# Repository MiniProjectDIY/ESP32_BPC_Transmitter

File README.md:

# ESP32_BPC_Transmitter
Trasmit BPC time signal with ESP32 and a customized PCB

https://youtu.be/aWq-_jqWnzw

Hardware:Fine tune the LC parameter to 68.5Khz resonance frequency

Software:Modify the wifi ssid and wifi password,flash the micropython firmware and upload the python code

The transmission distance is approximately two meters, but it will vary depending on your inductor.

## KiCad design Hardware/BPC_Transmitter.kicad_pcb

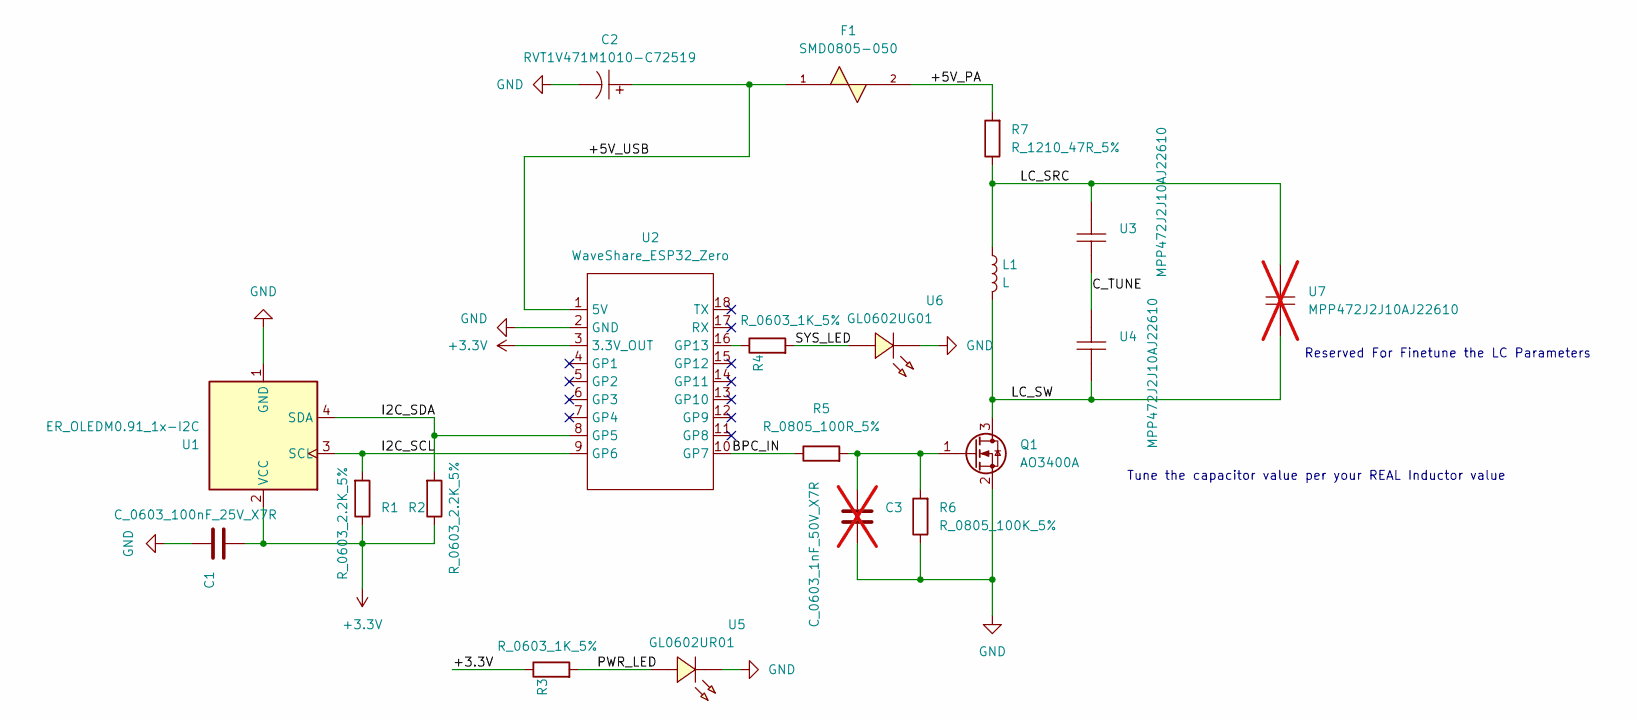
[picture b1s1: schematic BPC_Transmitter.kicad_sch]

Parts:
C1: C_0603_100nF_25V_X7R; C_0603_1608Metric
C2: RVT1V471M1010-C72519; CAP-SMD_BD10.0-L10.3-W10.3-LS11.0-R-RD; LCSC C72519
C3: C_0603_1nF_50V_X7R; C_0603_1608Metric; not fitted
F1: SMD0805-050; F0805; LCSC C66452
L1: L; Rod_Inductor_15mm
Q1: AO3400A; SOT-23
R1, R2: R_0603_2.2K_5%; R_0603_1608Metric
R3, R4: R_0603_1K_5%; R_0603_1608Metric
R5: R_0805_100R_5%; R_0805_2012Metric
R6: R_0805_100K_5%; R_0805_2012Metric
R7: R_1210_47R_5%; R_1210_3225Metric
U1: ER_OLEDM0.91_1x-I2C
U2: WaveShare_ESP32_Zero
U3, U4: MPP472J2J10AJ22610; CAP-TH_L11.4-W4.3-P10.00-D0.6; LCSC C506828
U5: GL0602UR01; LED-SMD_L1.6-W1.1-R-RD; LCSC C51933323
U6: GL0602UG01; LED-SMD_L1.6-W1.1-R-RD; LCSC C51933323
U7: MPP472J2J10AJ22610; CAP-TH_L11.4-W4.3-P10.00-D0.6; LCSC C506828; not fitted

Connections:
+3.3V: C1.2, R1.1, R2.1, R3.1, U1.2 (VCC), U2.3 (3.3V_OUT)
/+5V_PA: F1.2, R7.2
/+5V_USB: C2.1, F1.1, U2.1 (5V)
/BPC_IN: R5.1, U2.10 (GP7)
/C_TUNE: U3.1, U4.2
/I2C_SCL: R1.2, U1.3 (SCL), U2.9 (GP6)
/I2C_SDA: R2.2, U1.4 (SDA), U2.8 (GP5)
/LC_SRC: L1.1, R7.1, U3.2, U7.2
/LC_SW: L1.2, Q1.3 (D), U4.1, U7.1
/PWR_LED: R3.2, U5.1 (A)
/SYS_LED: R4.2, U6.1 (A)
GND: C1.1, C2.2, C3.2, Q1.2 (S), R6.1, U1.1 (GND), U2.2 (GND), U5.2 (C), U6.2 (C)
unnamed: C3.1, Q1.1 (G), R5.2, R6.2
unnamed: R4.1, U2.16 (GP13)

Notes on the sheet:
Reserved For Finetune the LC Parameters
Tune the capacitor value per your REAL Inductor value

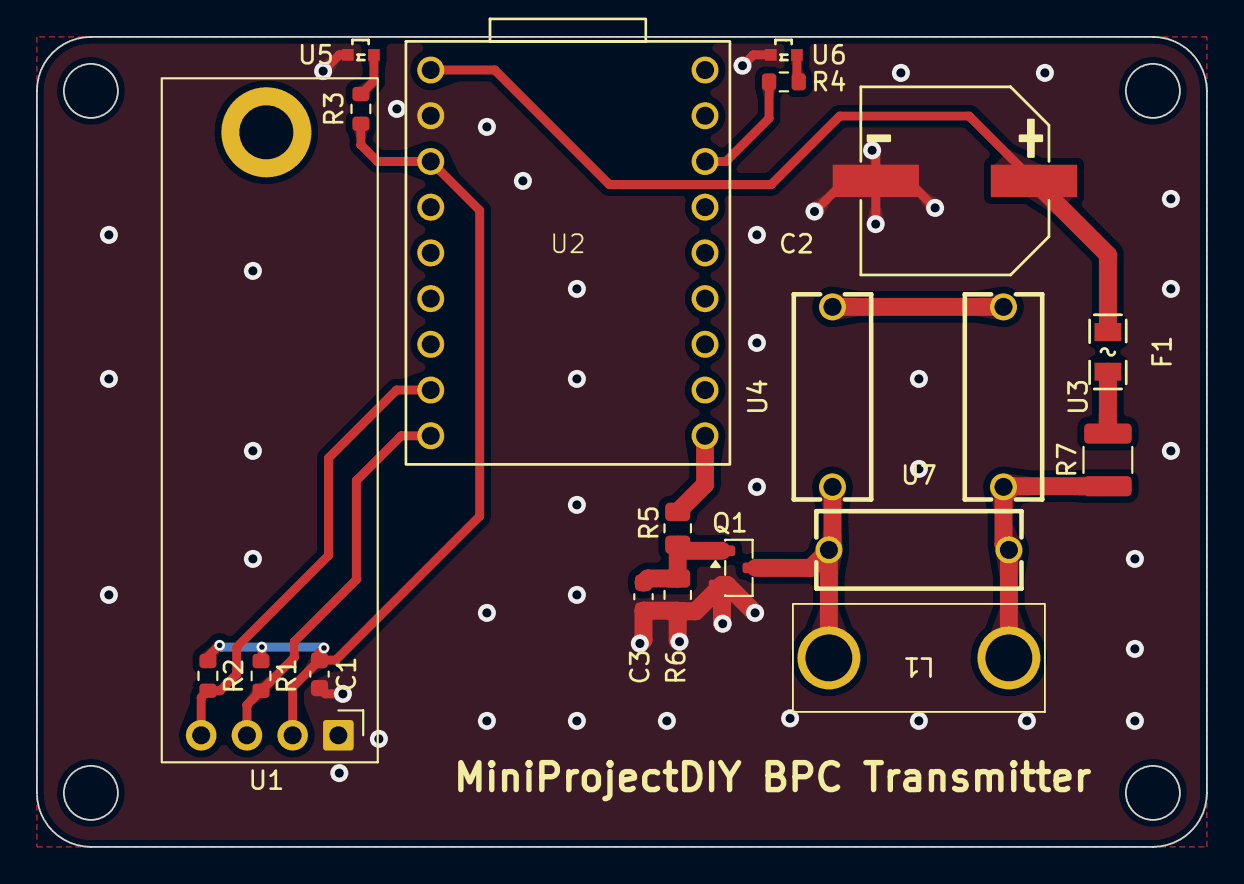
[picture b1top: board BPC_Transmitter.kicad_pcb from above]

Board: 2 copper layers, 65.0 x 45.0 mm, 20 parts (0 on the bottom side), 14 nets.
